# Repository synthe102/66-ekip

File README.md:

# 66-ekip
66 Ekip is a drop-in replacement PCB for the CA66 keyboard.

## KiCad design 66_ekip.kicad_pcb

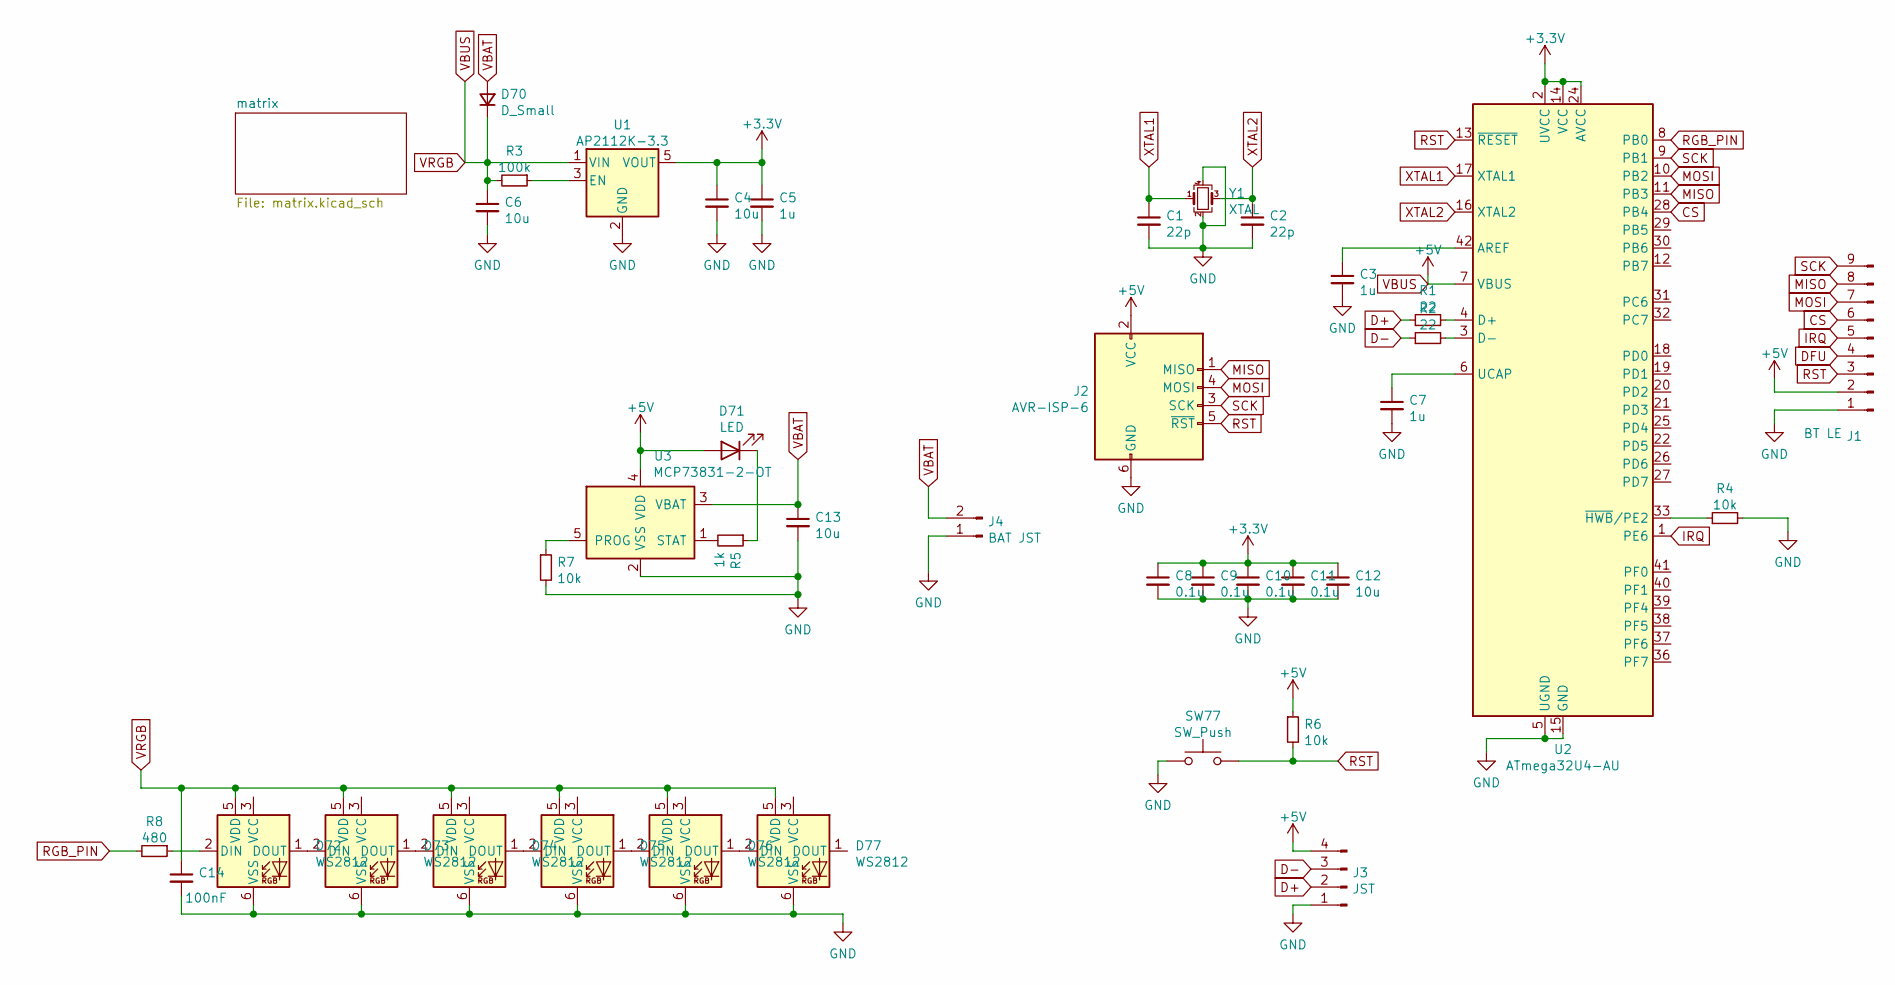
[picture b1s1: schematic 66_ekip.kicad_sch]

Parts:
C1, C2: 22p; C_0805_2012Metric
C3, C5, C7: 1u; C_0805_2012Metric
C4, C6, C12, C13: 10u; C_0805_2012Metric
C8, C9, C10, C11: 0.1u; C_0805_2012Metric
C14: 100nF; C_0805_2012Metric
D70: D_Small; D_0805_2012Metric
D71: LED; LED_0805_2012Metric
D72, D73, D74, D75, D76, D77: WS2812; LED_WS2812_PLCC6_5.0x5.0mm_P1.6mm
J1: BT LE; PinHeader_1x09_P1.00mm_Vertical
J2: AVR-ISP-6; Reset_Pretty
J3: JST; JST_SH_SM04B-SRSS-TB_1x04-1MP_P1.00mm_Horizontal
J4: BAT JST; JST_PH_S2B-PH-SM4-TB_1x02-1MP_P2.00mm_Horizontal
R1, R2: 22; R_0805_2012Metric
R3: 100k; R_0805_2012Metric
R4, R6, R7: 10k; R_0805_2012Metric
R5: 1k; R_0805_2012Metric
R8: 480; R_0805_2012Metric
SW77: SW_Push; SW_SPST_SKQG_WithStem
U1: AP2112K-3.3; SOT-23-5
U2: ATmega32U4-AU; TQFP-44_10x10mm_P0.8mm
U3: MCP73831-2-OT; SOT-23-5
Y1: XTAL; Crystal_SMD_3225-4Pin_3.2x2.5mm

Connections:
+3V3: C4.1, C5.1, C8.1, C9.1, C10.1, C11.1, C12.1, U1.5 (VOUT), U2.2 (UVCC), U2.14 (VCC), U2.24 (AVCC), U2.34 (VCC), U2.44 (AVCC)
CS: J1.6, U2.28 (PB4)
D+: J3.2, R1.1
D-: J3.3, R2.1
GND: C1.2, C2.2, C3.2, C4.2, C5.2, C6.2, C7.2, C8.2, C9.2, C10.2, C11.2, C12.2, C13.2, C14.2, D72.6 (VSS), D73.6 (VSS), D74.6 (VSS), D75.6 (VSS), D76.6 (VSS), D77.6 (VSS), J1.1, J2.6 (GND), J3.1, J4.1, R4.2, R7.2, SW77.1, U1.2 (GND), U2.5 (UGND), U2.15 (GND), U2.23 (GND), U2.35 (GND), U2.43 (GND), U3.2 (VSS), Y1.2, Y1.4
IRQ: J1.5, U2.1 (PE6)
MISO: J1.8, J2.1 (MISO), U2.11 (PB3)
MOSI: J1.7, J2.4 (MOSI), U2.10 (PB2)
unnamed: C3.1, U2.42 (AREF)
unnamed: C7.1, U2.6 (UCAP)
unnamed: D71.1 (K), R5.1
unnamed: D72.1 (DOUT), D73.2 (DIN)
unnamed: D72.2 (DIN), R8.1
unnamed: D73.1 (DOUT), D74.2 (DIN)
unnamed: D74.1 (DOUT), D75.2 (DIN)
unnamed: D75.1 (DOUT), D76.2 (DIN)
unnamed: D76.1 (DOUT), D77.2 (DIN)
unnamed: R1.2, U2.4 (D+)
unnamed: R2.2, U2.3 (D-)
unnamed: R3.1, U1.3 (EN)
unnamed: R4.1, U2.33 (~HWB~/PE2)
unnamed: R5.2, U3.1 (STAT)
unnamed: R7.1, U3.5 (PROG)
RGB_PIN: R8.2, U2.8 (PB0)
RST: J1.3, J2.5 (~RST), R6.2, SW77.2, U2.13 (~RESET)
SCK: J1.9, J2.3 (SCK), U2.9 (PB1)
VBAT: C13.1, D70.2 (A), J4.2, U3.3 (VBAT)
VBUS: C6.1, C14.1, D70.1 (K), D71.2 (A), D72.5 (VDD), D73.5 (VDD), D74.5 (VDD), D75.5 (VDD), D76.5 (VDD), D77.5 (VDD), J1.2, J2.2 (VCC), J3.4, R3.2, R6.1, U1.1 (VIN), U2.7 (VBUS), U3.4 (VDD)
XTAL1: C1.1, U2.17 (XTAL1), Y1.1
XTAL2: C2.1, U2.16 (XTAL2), Y1.3

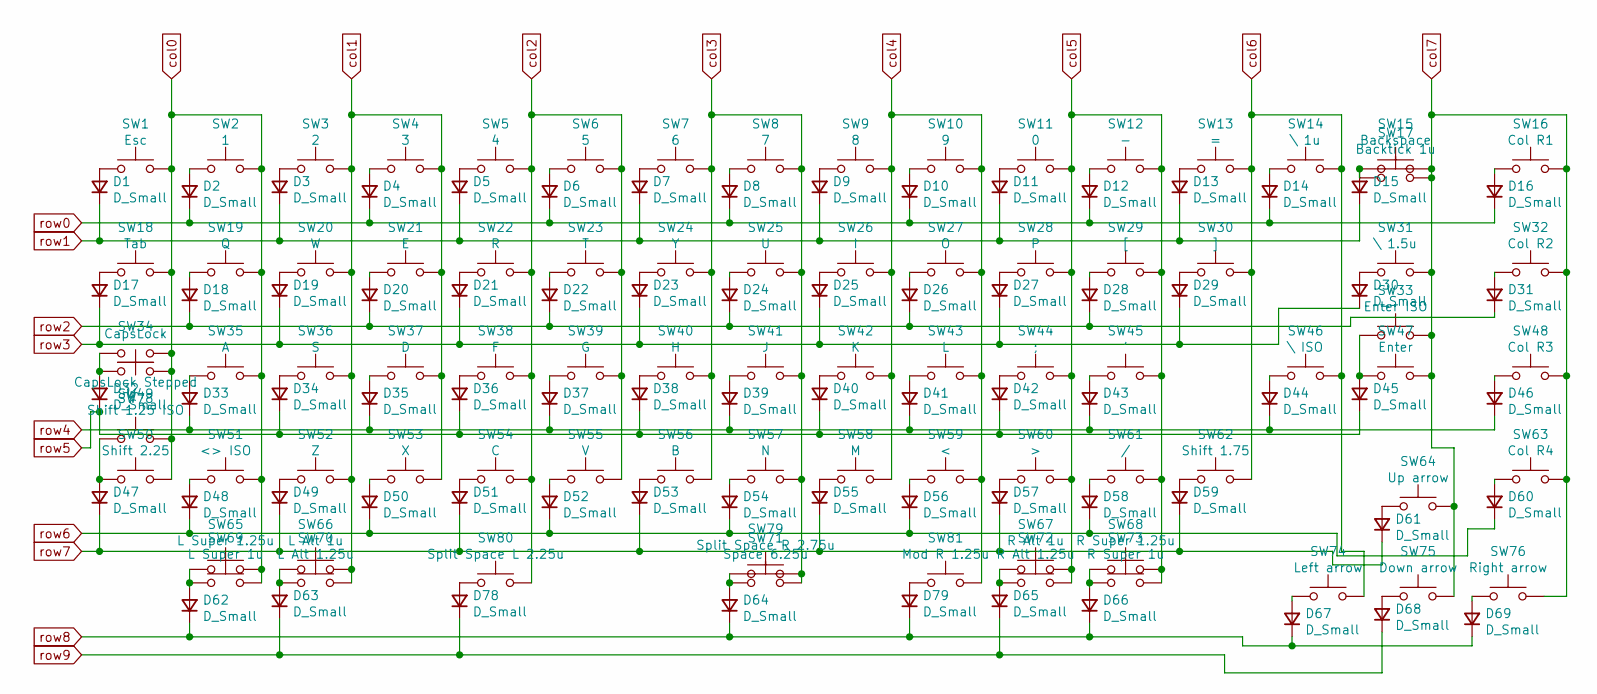
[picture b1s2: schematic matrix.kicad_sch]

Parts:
D1, D2, D3, D4, D5, D6, D7, D8, D9, D10, D11, D12, D13, D14, D15, D16, D17, D18, D19, D20, D21, D22, D23, D24, D25, D26, D27, D28, D29, D30, D31, D32, D33, D34, D35, D36, D37, D38, D39, D40, D41, D42, D43, D44, D45, D46, D47, D48, D49, D50, D51, D52, D53, D54, D55, D56, D57, D58, D59, D60, D61, D62, D63, D64, D65, D66, D67, D68, D69, D78, D79: D_Small; D_0805_2012Metric
SW1: Esc; MX-1U-NoLED
SW2: 1; MX-1U-NoLED
SW3: 2; MX-1U-NoLED
SW4: 3; MX-1U-NoLED
SW5: 4; MX-1U-NoLED
SW6: 5; MX-1U-NoLED
SW7: 6; MX-1U-NoLED
SW8: 7; MX-1U-NoLED
SW9: 8; MX-1U-NoLED
SW10: 9; MX-1U-NoLED
SW11: 0; MX-1U-NoLED
SW12: -; MX-1U-NoLED
SW13: =; MX-1U-NoLED
SW14: \ 1u; MX-1U-NoLED
SW15: Backspace; MX-2U-NoLED
SW16: Col R1; MX-1U-NoLED
SW17: Backtick 1u; MX-1U-NoLED
SW18: Tab; MX-1.5U-NoLED
SW19: Q; MX-1U-NoLED
SW20: W; MX-1U-NoLED
SW21: E; MX-1U-NoLED
SW22: R; MX-1U-NoLED
SW23: T; MX-1U-NoLED
SW24: Y; MX-1U-NoLED
SW25: U; MX-1U-NoLED
SW26: I; MX-1U-NoLED
SW27: O; MX-1U-NoLED
SW28: P; MX-1U-NoLED
SW29: [; MX-1U-NoLED
SW30: ]; MX-1U-NoLED
SW31: \ 1.5u; MX-1.5U-NoLED
SW32: Col R2; MX-1U-NoLED
SW33: Enter ISO; MX-ISO-ReversedStabilizers-NoLED
SW34: CapsLock; MX-1.75U-NoLED
SW35: A; MX-1U-NoLED
SW36: S; MX-1U-NoLED
SW37: D; MX-1U-NoLED
SW38: F; MX-1U-NoLED
SW39: G; MX-1U-NoLED
SW40: H; MX-1U-NoLED
SW41: J; MX-1U-NoLED
SW42: K; MX-1U-NoLED
SW43: L; MX-1U-NoLED
SW44: ;; MX-1U-NoLED
SW45: '; MX-1U-NoLED
SW46: \ ISO; MX-1U-NoLED
SW47: Enter; MX-2.25U-ReversedStabilizers-NoLED
SW48: Col R3; MX-1U-NoLED
SW49: Shift 1.25 ISO; MX-1.25U-NoLED
SW50: Shift 2.25; MX-2.25U-ReversedStabilizers-NoLED
SW51: <> ISO; MX-1U-NoLED
SW52: Z; MX-1U-NoLED
SW53: X; MX-1U-NoLED
SW54: C; MX-1U-NoLED
SW55: V; MX-1U-NoLED
SW56: B; MX-1U-NoLED
SW57: N; MX-1U-NoLED
SW58: M; MX-1U-NoLED
SW59: <; MX-1U-NoLED
SW60: >; MX-1U-NoLED
SW61: /; MX-1U-NoLED
SW62: Shift 1.75; MX-1.75U-NoLED
SW63: Col R4; MX-1U-NoLED
SW64: Up arrow; MX-1U-NoLED
SW65: L Super 1.25u; MX-1.25U-NoLED
SW66: L Alt 1u; MX-1U-NoLED
SW67: R Alt 1u; MX-1U-NoLED
SW68: R Super 1.25u; MX-1.25U-NoLED
SW69: L Super 1u; MX-1U-NoLED
SW70: L Alt 1.25u; MX-1.25U-NoLED
SW71: Space 6.25u; MX-6.25U-ReversedStabilizers-NoLED
SW72: R Alt 1.25u; MX-1.25U-NoLED
SW73: R Super 1u; MX-1U-NoLED
SW74: Left arrow; MX-1U-NoLED
SW75: Down arrow; MX-1U-NoLED
SW76: Right arrow; MX-1U-NoLED
SW78: CapsLock Stepped; MX-1.25U-NoLED
SW79: Split Space R 2.75u; MX-2.75U-ReversedStabilizers-NoLED
SW80: Split Space L 2.25u; MX-2.25U-ReversedStabilizers-NoLED
SW81: Mod R 1.25u; MX-1.25U-NoLED

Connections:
unnamed: D1.2 (A), SW1.1
unnamed: D2.2 (A), SW2.1
unnamed: D3.2 (A), SW3.1
unnamed: D4.2 (A), SW4.1
unnamed: D5.2 (A), SW5.1
unnamed: D6.2 (A), SW6.1
unnamed: D7.2 (A), SW7.1
unnamed: D8.2 (A), SW8.1
unnamed: D9.2 (A), SW9.1
unnamed: D10.2 (A), SW10.1
unnamed: D11.2 (A), SW11.1
unnamed: D12.2 (A), SW12.1
unnamed: D13.2 (A), SW13.1
unnamed: D14.2 (A), SW14.1
unnamed: D15.2 (A), SW15.1, SW17.1
unnamed: D16.2 (A), SW16.1
unnamed: D17.2 (A), SW18.1
unnamed: D18.2 (A), SW19.1
unnamed: D19.2 (A), SW20.1
unnamed: D20.2 (A), SW21.1
unnamed: D21.2 (A), SW22.1
unnamed: D22.2 (A), SW23.1
unnamed: D23.2 (A), SW24.1
unnamed: D24.2 (A), SW25.1
unnamed: D25.2 (A), SW26.1
unnamed: D26.2 (A), SW27.1
unnamed: D27.2 (A), SW28.1
unnamed: D28.2 (A), SW29.1
unnamed: D29.2 (A), SW30.1
unnamed: D30.2 (A), SW31.1
unnamed: D31.2 (A), SW32.1
unnamed: D32.2 (A), SW34.1, SW78.2
unnamed: D33.2 (A), SW35.1
unnamed: D34.2 (A), SW36.1
unnamed: D35.2 (A), SW37.1
unnamed: D36.2 (A), SW38.1
unnamed: D37.2 (A), SW39.1
unnamed: D38.2 (A), SW40.1
unnamed: D39.2 (A), SW41.1
unnamed: D40.2 (A), SW42.1
unnamed: D41.2 (A), SW43.1
unnamed: D42.2 (A), SW44.1
unnamed: D43.2 (A), SW45.1
unnamed: D44.2 (A), SW46.1
unnamed: D45.2 (A), SW33.1, SW47.1
unnamed: D46.2 (A), SW48.1
unnamed: D47.2 (A), SW49.1, SW50.1
unnamed: D48.2 (A), SW51.1
unnamed: D49.2 (A), SW52.1
unnamed: D50.2 (A), SW53.1
unnamed: D51.2 (A), SW54.1
unnamed: D52.2 (A), SW55.1
unnamed: D53.2 (A), SW56.1
unnamed: D54.2 (A), SW57.1
unnamed: D55.2 (A), SW58.1
unnamed: D56.2 (A), SW59.1
unnamed: D57.2 (A), SW60.1
unnamed: D58.2 (A), SW61.1
unnamed: D59.2 (A), SW62.1
unnamed: D60.2 (A), SW63.1
unnamed: D61.2 (A), SW64.1
unnamed: D62.2 (A), SW65.1, SW69.1
unnamed: D63.2 (A), SW66.1, SW70.1
unnamed: D64.2 (A), SW71.1, SW79.1
unnamed: D65.2 (A), SW67.1, SW72.1
unnamed: D66.2 (A), SW68.1, SW73.1
unnamed: D67.2 (A), SW74.1
unnamed: D68.2 (A), SW75.1
unnamed: D69.2 (A), SW76.1
unnamed: D78.2 (A), SW80.1
unnamed: D79.2 (A), SW81.1
col0: SW1.2, SW2.2, SW18.2, SW19.2, SW34.2, SW35.2, SW49.2, SW50.2, SW51.2, SW65.2, SW69.2, SW78.1
col1: SW3.2, SW4.2, SW20.2, SW21.2, SW36.2, SW37.2, SW52.2, SW53.2, SW66.2, SW70.2
col2: SW5.2, SW6.2, SW22.2, SW23.2, SW38.2, SW39.2, SW54.2, SW55.2, SW80.2
col3: SW7.2, SW8.2, SW24.2, SW25.2, SW40.2, SW41.2, SW56.2, SW57.2, SW71.2, SW79.2
col4: SW9.2, SW10.2, SW26.2, SW27.2, SW42.2, SW43.2, SW58.2, SW59.2, SW81.2
col5: SW11.2, SW12.2, SW28.2, SW29.2, SW44.2, SW45.2, SW60.2, SW61.2, SW67.2, SW68.2, SW72.2, SW73.2
col6: SW13.2, SW14.2, SW30.2, SW46.2, SW62.2, SW74.2
col7: SW15.2, SW16.2, SW17.2, SW31.2, SW32.2, SW33.2, SW47.2, SW48.2, SW63.2, SW64.2, SW75.2, SW76.2
row0: D2.1 (K), D4.1 (K), D6.1 (K), D8.1 (K), D10.1 (K), D12.1 (K), D14.1 (K), D16.1 (K)
row1: D1.1 (K), D3.1 (K), D5.1 (K), D7.1 (K), D9.1 (K), D11.1 (K), D13.1 (K), D15.1 (K)
row2: D18.1 (K), D20.1 (K), D22.1 (K), D24.1 (K), D26.1 (K), D28.1 (K), D31.1 (K)
row3: D17.1 (K), D19.1 (K), D21.1 (K), D23.1 (K), D25.1 (K), D27.1 (K), D29.1 (K), D30.1 (K)
row4: D33.1 (K), D35.1 (K), D37.1 (K), D39.1 (K), D41.1 (K), D43.1 (K), D44.1 (K), D46.1 (K)
row5: D32.1 (K), D34.1 (K), D36.1 (K), D38.1 (K), D40.1 (K), D42.1 (K), D45.1 (K)
row6: D48.1 (K), D50.1 (K), D52.1 (K), D54.1 (K), D56.1 (K), D58.1 (K), D60.1 (K)
row7: D47.1 (K), D49.1 (K), D51.1 (K), D53.1 (K), D55.1 (K), D57.1 (K), D59.1 (K), D61.1 (K)
row8: D62.1 (K), D64.1 (K), D66.1 (K), D67.1 (K), D69.1 (K), D79.1 (K)
row9: D63.1 (K), D65.1 (K), D68.1 (K), D78.1 (K)

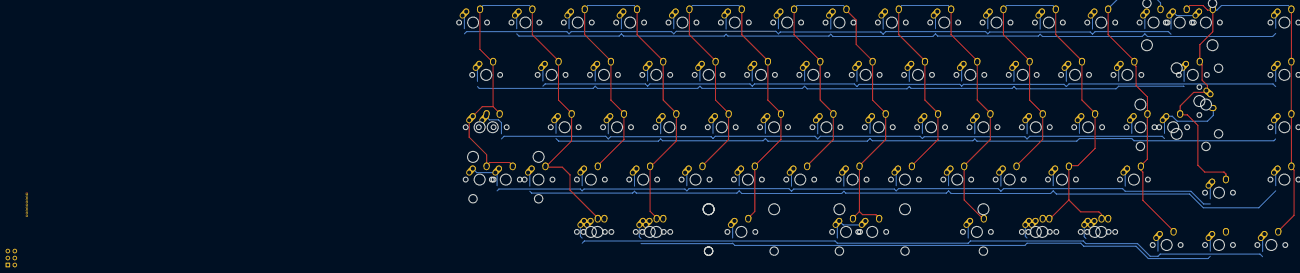
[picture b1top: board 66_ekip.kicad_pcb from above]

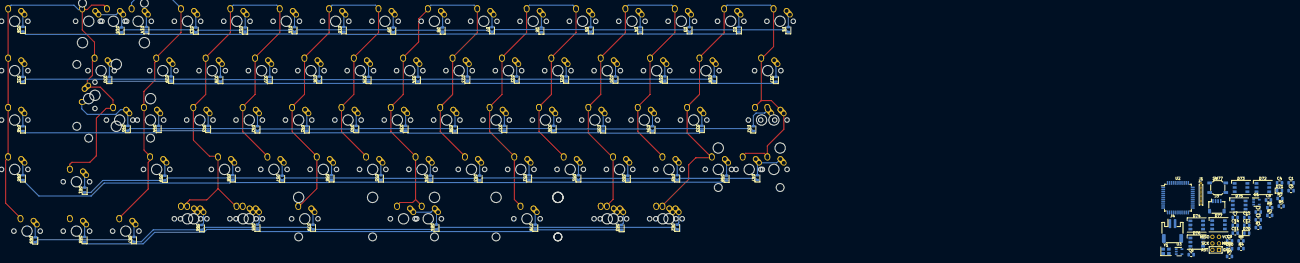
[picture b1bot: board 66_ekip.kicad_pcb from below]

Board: 2 copper layers, 190 parts (110 on the bottom side), 119 nets.

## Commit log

2021-05-15 Add gitignore
2021-05-15 Initialize kicad project
2021-05-15 Add submodules for librairies
2021-05-16 Matrix routed on the PCB
2021-05-16 Update gitignore with cache files
2021-05-16 Add ISO Enter NOLED FLipped stabs MX_ALPS
2021-05-16 Add files after gitignore update
2021-05-16 Add useful files
